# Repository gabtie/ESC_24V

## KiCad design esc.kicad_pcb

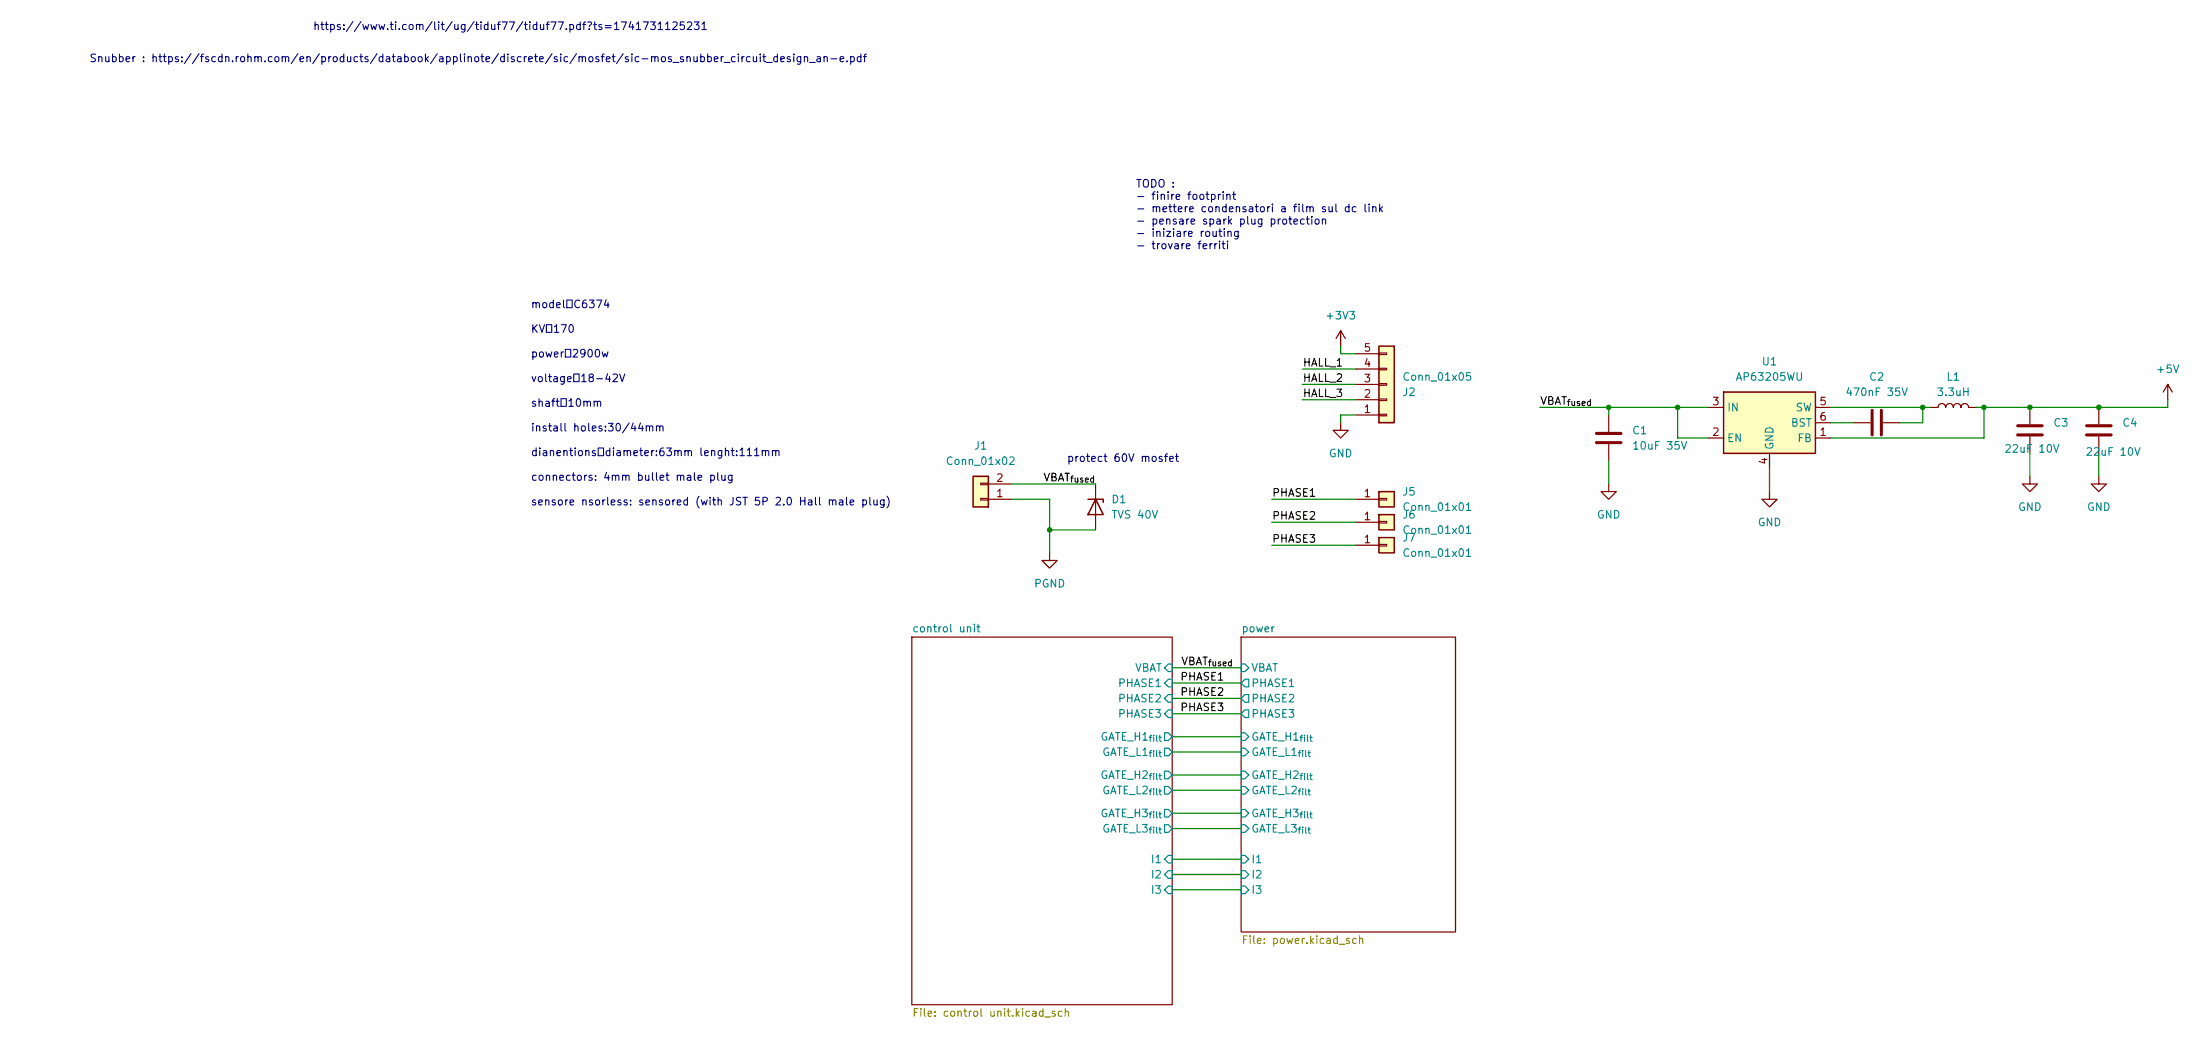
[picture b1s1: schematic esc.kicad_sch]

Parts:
C1: 10uF 35V; C_0603_1608Metric
C2: 470nF 35V; C_0603_1608Metric
C3, C4: 22uF 10V; C_0603_1608Metric
D1: TVS 40V; D_SMA
J1: Conn_01x02; AMASS_XT60-F_1x02_P7.20mm_Vertical
J2: Conn_01x05; JST_PH_B5B-PH-K_1x05_P2.00mm_Vertical
J5, J6, J7: Conn_01x01; MountingHole_3mm_Pad_Via
L1: 3.3uH; L_Wuerth_HCI-7040
U1: AP63205WU; TSOT-23-6

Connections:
+3V3: J2.5; also elsewhere on the board
+5V: C3.1, C4.1, L1.2, U1.1 (FB); also elsewhere on the board
/HALL_1: J2.4
/HALL_2: J2.3
/HALL_3: J2.2
/PHASE1: J5.1 (Pin_1_1); also elsewhere on the board
/PHASE2: J6.1 (Pin_1_1); also elsewhere on the board
/PHASE3: J7.1 (Pin_1_1); also elsewhere on the board
/VBAT_{fused}: C1.1, D1.1 (K), J1.2, U1.2 (EN), U1.3 (IN); also elsewhere on the board
GND: C1.2, C3.2, C4.2, J2.1, U1.4 (GND); also elsewhere on the board
unnamed: C2.1, U1.6 (BST)
unnamed: C2.2, L1.1, U1.5 (SW)
PGND: D1.2 (A), J1.1; also elsewhere on the board

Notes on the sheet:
https://www.ti.com/lit/ug/tiduf77/tiduf77.pdf?ts=1741731125231
model：C6374 KV：170 power：2900w voltage：18-42V shaft：10mm install holes:30/44mm dianentions：diameter:63mm lenght:111mm connectors: 4mm bullet male plug sensore nsorless: sensored (with JST 5P 2.0 Hall male plug)
protect 60V mosfet
Snubber : https://fscdn.rohm.com/en/products/databook/applinote/discrete/sic/mosfet/sic-mos_snubber_circuit_design_an-e.pdf
TODO : - finire footprint - mettere condensatori a film sul dc link - pensare spark plug protection - iniziare routing - trovare ferriti

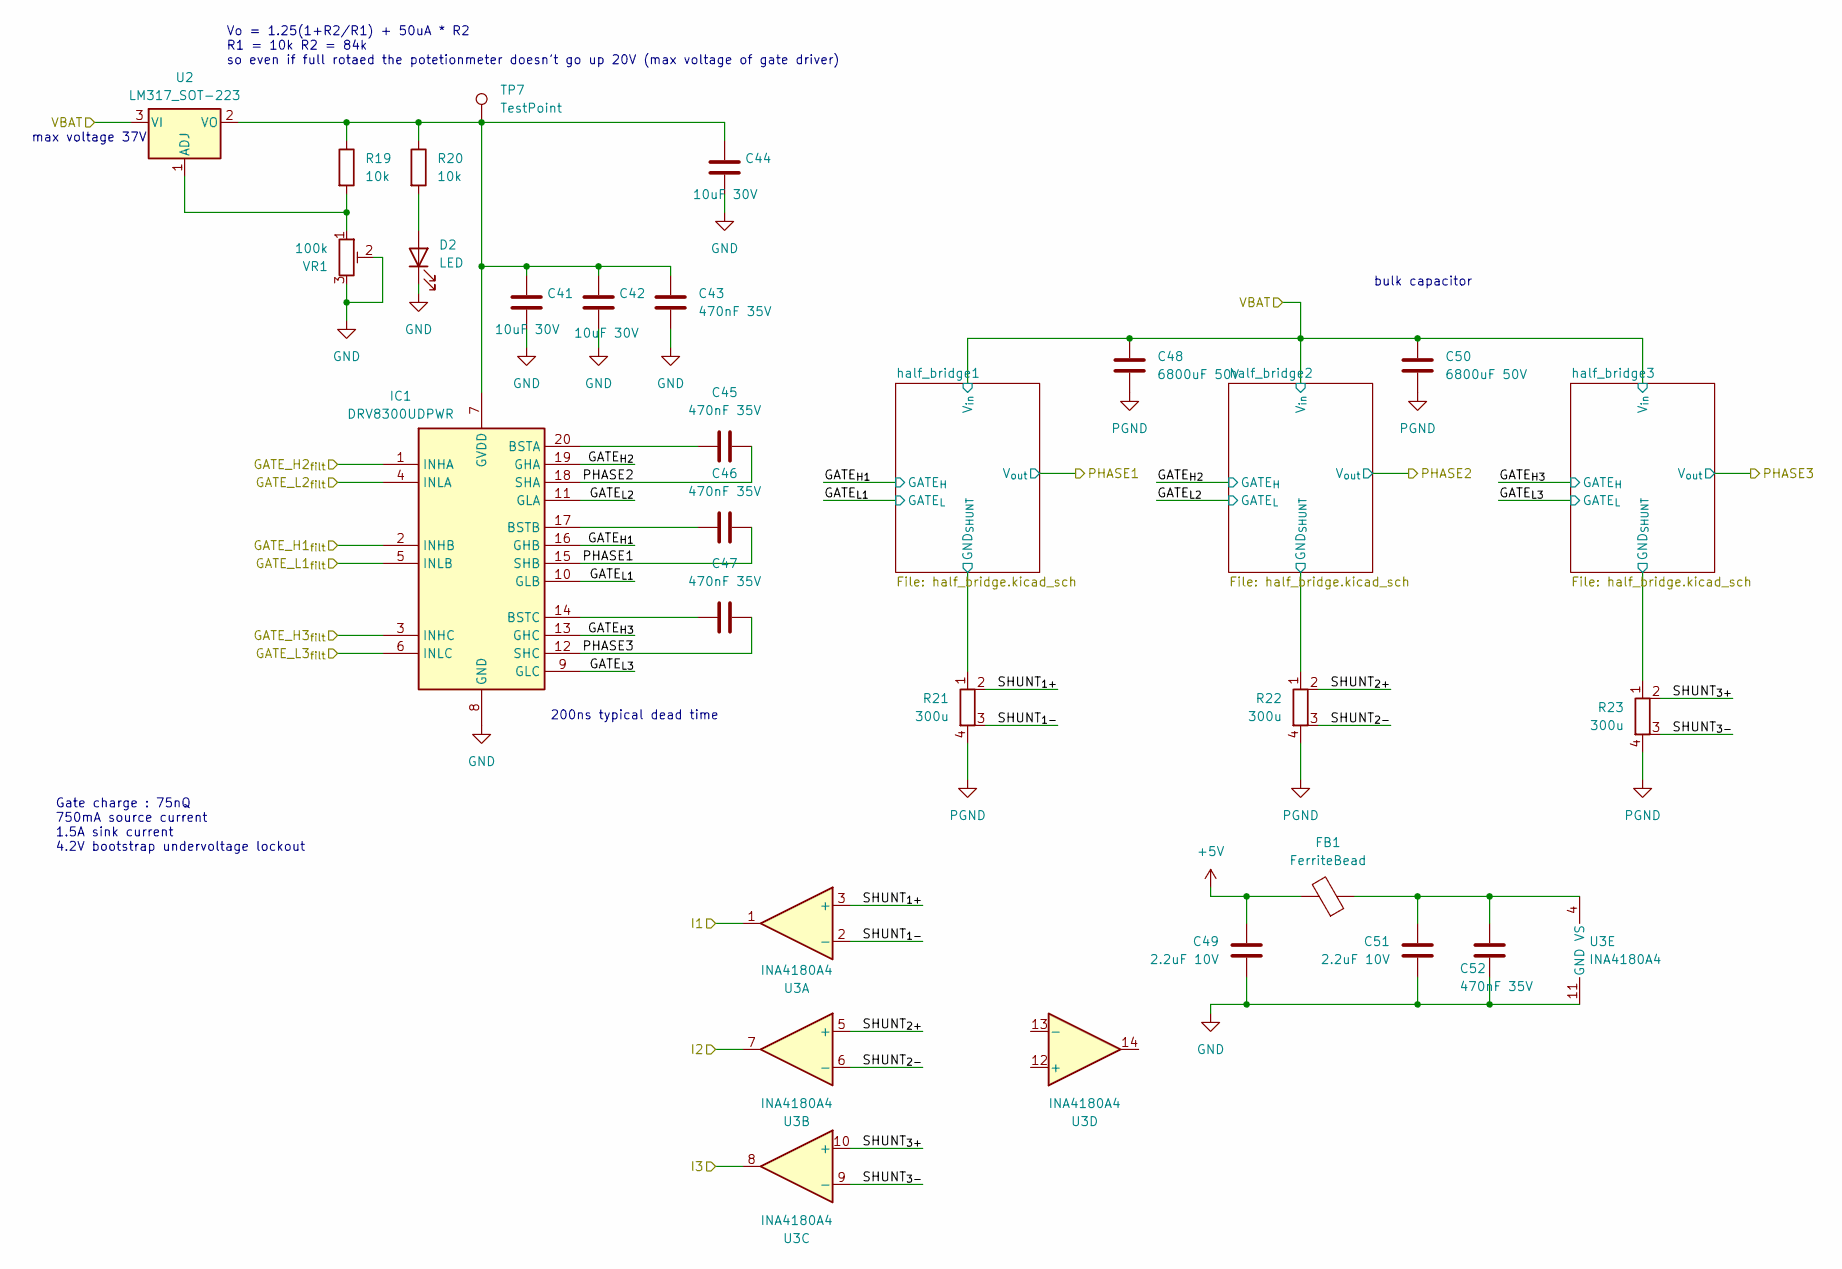
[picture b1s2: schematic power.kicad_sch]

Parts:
C41, C42: 10uF 30V; C_0603_1608Metric
C43, C45, C46, C47, C52: 470nF 35V; C_0603_1608Metric
C44: 10uF 30V; C_Radial_D5.0mm_H11.0mm_P2.00mm
C48, C50: 6800uF 50V; C_Radial_D18.0mm_H35.5mm_P7.50mm
C49, C51: 2.2uF 10V; C_0603_1608Metric
D2: LED; LED_0603_1608Metric
FB1: FerriteBead; L_0805_2012Metric
IC1: DRV8300UDPWR; gate_driver_SOP65P640X120-20N; Mouser Part Number 595-DRV8300UDPWR
R19, R20: 10k; R_0603_1608Metric
R21, R22, R23: 300u; HCSK1216FTL300
TP7: TestPoint; TestPoint_Pad_D1.0mm
U2: LM317_SOT-223; SOT-223-3_TabPin2
U3: INA4180A4; TSSOP-14_4.4x5mm_P0.65mm
VR1: 100k; Potentiometer_Bourns_3214W_Vertical

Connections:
+5V: C49.1, FB1.2; also elsewhere on the board
/PHASE1: C46.2, IC1.15 (SHB); also elsewhere on the board
/PHASE2: C45.2, IC1.18 (SHA); also elsewhere on the board
/PHASE3: C47.2, IC1.12 (SHC); also elsewhere on the board
/VBAT_{fused}: C48.1, C50.1, U2.3 (VI); also elsewhere on the board
/control unit/GATE_H1_{filt}: IC1.2 (INHB); also elsewhere on the board
/control unit/GATE_H2_{filt}: IC1.1 (INHA); also elsewhere on the board
/control unit/GATE_H3_{filt}: IC1.3 (INHC); also elsewhere on the board
/control unit/GATE_L1_{filt}: IC1.5 (INLB); also elsewhere on the board
/control unit/GATE_L2_{filt}: IC1.4 (INLA); also elsewhere on the board
/control unit/GATE_L3_{filt}: IC1.6 (INLC); also elsewhere on the board
/control unit/I1: U3.1; also elsewhere on the board
/control unit/I2: U3.7; also elsewhere on the board
/control unit/I3: U3.8; also elsewhere on the board
/power/GATE_{H1}: IC1.16 (GHB); also elsewhere on the board
/power/GATE_{H2}: IC1.19 (GHA); also elsewhere on the board
/power/GATE_{H3}: IC1.13 (GHC); also elsewhere on the board
/power/GATE_{L1}: IC1.10 (GLB); also elsewhere on the board
/power/GATE_{L2}: IC1.11 (GLA); also elsewhere on the board
/power/GATE_{L3}: IC1.9 (GLC); also elsewhere on the board
/power/SHUNT_{1+}: R21.2, U3.3 (+)
/power/SHUNT_{1-}: R21.3, U3.2 (-)
/power/SHUNT_{2+}: R22.2, U3.5 (+)
/power/SHUNT_{2-}: R22.3, U3.6 (-)
/power/SHUNT_{3+}: R23.2, U3.10 (+)
/power/SHUNT_{3-}: R23.3, U3.9 (-)
/power/half_bridge1/GND_{SHUNT}: R21.1; also elsewhere on the board
/power/half_bridge2/GND_{SHUNT}: R22.1; also elsewhere on the board
/power/half_bridge3/GND_{SHUNT}: R23.1; also elsewhere on the board
GND: C41.2, C42.2, C43.2, C44.2, C49.2, C51.2, C52.1, D2.1 (K), IC1.8 (GND), U3.11 (GND), VR1.2, VR1.3; also elsewhere on the board
unnamed: D2.2 (A), R20.2
unnamed: C45.1, IC1.20 (BSTA)
unnamed: C46.1, IC1.17 (BSTB)
unnamed: C47.1, IC1.14 (BSTC)
unnamed: C41.1, C42.1, C43.1, C44.1, IC1.7 (GVDD), R19.1, R20.1, TP7.1 (1_1), U2.2 (VO)
unnamed: R19.2, U2.1 (ADJ), VR1.1
unnamed: C51.1, C52.2, FB1.1, U3.4 (VS)
PGND: C48.2, C50.2, R21.4, R22.4, R23.4; also elsewhere on the board

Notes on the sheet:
max voltage 37V
bulk capacitor
Vo = 1.25(1+R2/R1) + 50uA * R2 R1 = 10k R2 = 84k so even if full rotaed the potetionmeter doesn't go up 20V (max voltage of gate driver)
200ns typical dead time
Gate charge : 75nQ 750mA source current 1.5A sink current 4.2V bootstrap undervoltage lockout

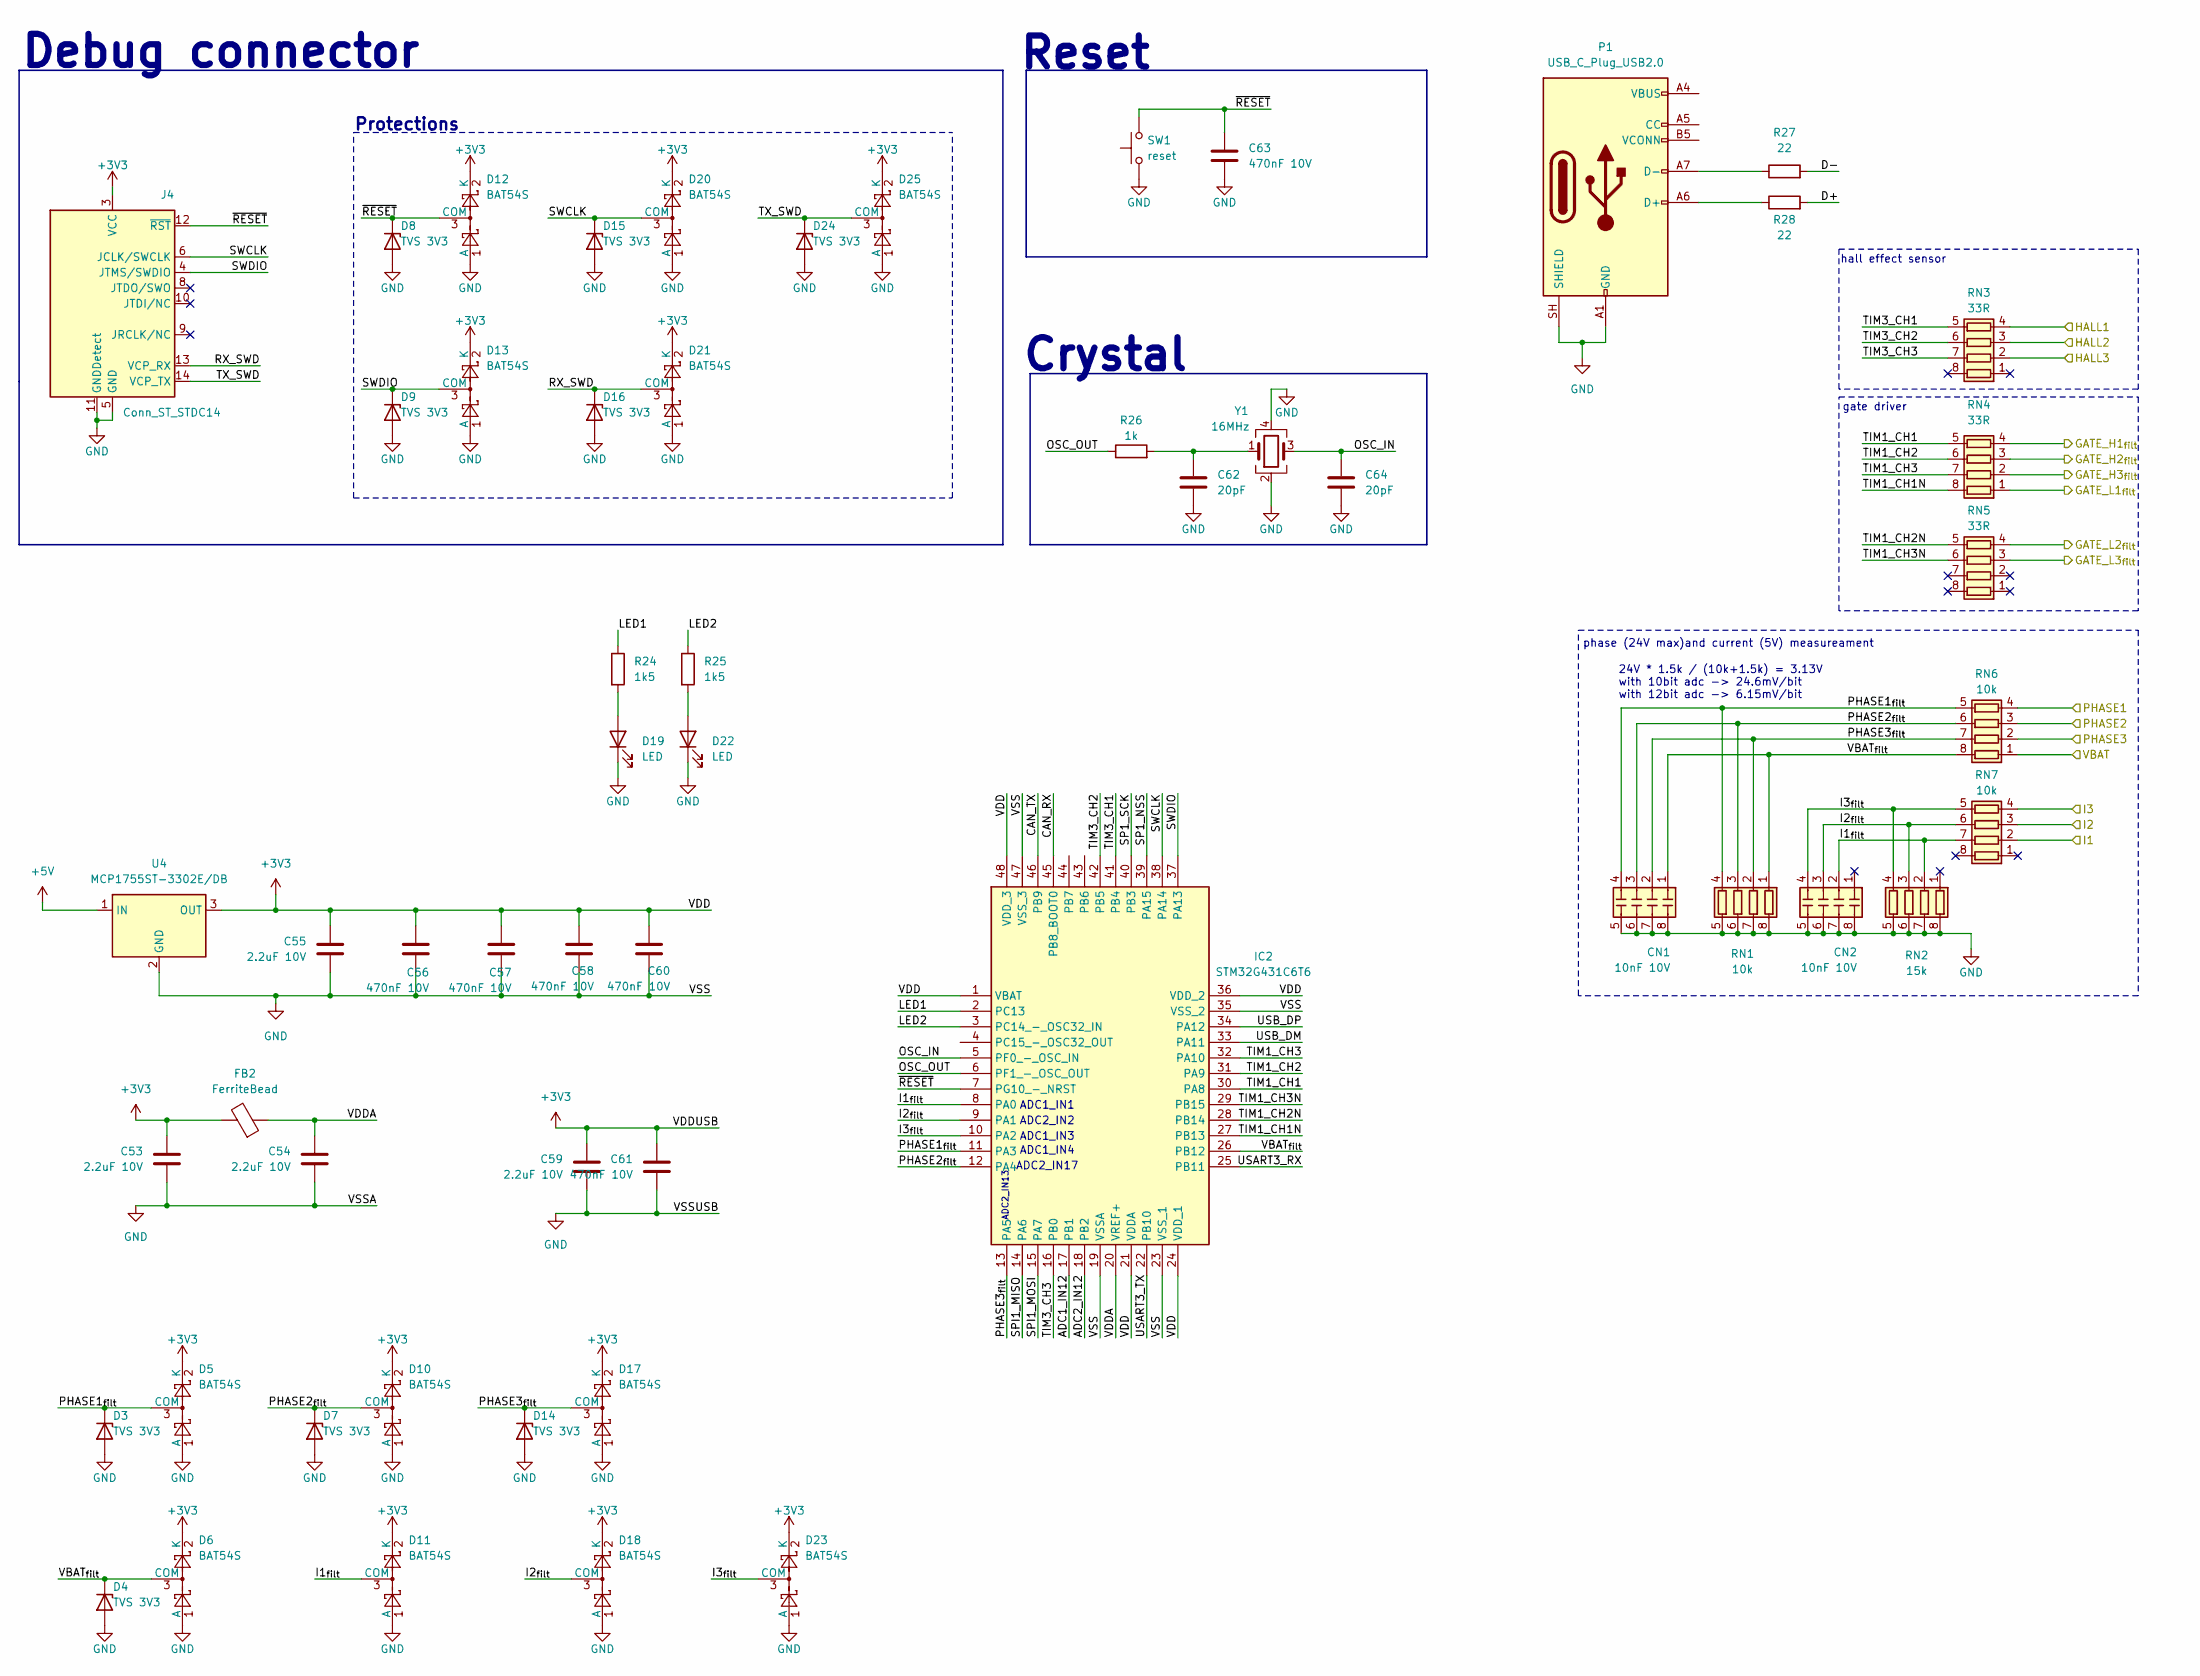
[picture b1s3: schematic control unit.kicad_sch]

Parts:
C53, C54, C55, C59: 2.2uF 10V; C_0603_1608Metric
C56, C57, C58, C60, C61, C63: 470nF 10V; C_0603_1608Metric
C62, C64: 20pF; C_0603_1608Metric
CN1, CN2: 10nF 10V; R_Array_Convex_4x0612
D3, D4, D7, D8, D9, D14, D15, D16, D24: TVS 3V3; D_SOD-523
D5, D6, D10, D11, D12, D13, D17, D18, D20, D21, D23, D25: BAT54S; SOT-23
D19, D22: LED; LED_0603_1608Metric
FB2: FerriteBead; L_0805_2012Metric
IC2: STM32G431C6T6; Mouser Part Number 511-STM32G431C6T6
J4: Conn_ST_STDC14; SAMTEC_FTSH-107-01-L-DV-K-TR
P1: USB_C_Plug_USB2.0
R24, R25: 1k5; R_0603_1608Metric
R26: 1k; R_0603_1608Metric
R27, R28: 22; R_0603_1608Metric
RN1, RN6, RN7: 10k; R_Array_Convex_4x0603
RN2: 15k; R_Array_Convex_4x0603
RN3, RN4, RN5: 33R; R_Array_Convex_4x0603
SW1: reset; SW_SPST_FSMSM
U4: MCP1755ST-3302E/DB; SOT-223-3_TabPin2
Y1: 16MHz; Crystal_SMD_EuroQuartz_MT-4Pin_3.2x2.5mm

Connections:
+3V3: C53.1, C55.1, C56.1, C57.1, C58.1, C59.1, C60.1, C61.1, D5.2 (K), D6.2 (K), D10.2 (K), D11.2 (K), D12.2 (K), D13.2 (K), D17.2 (K), D18.2 (K), D20.2 (K), D21.2 (K), D23.2 (K), D25.2 (K), FB2.2, IC2.1 (VBAT), IC2.21 (VDDA), IC2.24 (VDD_1), IC2.36 (VDD_2), IC2.48 (VDD_3), J4.3 (VCC), U4.3 (OUT); also elsewhere on the board
+5V: U4.1 (IN); also elsewhere on the board
/PHASE1: RN6.4 (R4.1); also elsewhere on the board
/PHASE2: RN6.3 (R3.1); also elsewhere on the board
/PHASE3: RN6.2 (R2.1); also elsewhere on the board
/VBAT_{fused}: RN6.1 (R1.1); also elsewhere on the board
/control unit/ADC1_IN12: IC2.17 (PB1)
/control unit/ADC2_IN12: IC2.18 (PB2)
/control unit/CAN_RX: IC2.45 (PB8_BOOT0)
/control unit/CAN_TX: IC2.46 (PB9)
/control unit/D+: R28.2
/control unit/D-: R27.2
/control unit/GATE_H1_{filt}: RN4.4 (R4.1); also elsewhere on the board
/control unit/GATE_H2_{filt}: RN4.3 (R3.1); also elsewhere on the board
/control unit/GATE_H3_{filt}: RN4.2 (R2.1); also elsewhere on the board
/control unit/GATE_L1_{filt}: RN4.1 (R1.1); also elsewhere on the board
/control unit/GATE_L2_{filt}: RN5.4 (R4.1); also elsewhere on the board
/control unit/GATE_L3_{filt}: RN5.3 (R3.1); also elsewhere on the board
/control unit/HALL1: RN3.4 (R4.1)
/control unit/HALL2: RN3.3 (R3.1)
/control unit/HALL3: RN3.2 (R2.1)
/control unit/I1: RN7.2 (R2.1); also elsewhere on the board
/control unit/I1_{filt}: CN2.2 (R2.1), D11.3 (COM), IC2.8 (PA0), RN2.2 (R2.1), RN7.7 (R2.2)
/control unit/I2: RN7.3 (R3.1); also elsewhere on the board
/control unit/I2_{filt}: CN2.3 (R3.1), D18.3 (COM), IC2.9 (PA1), RN2.3 (R3.1), RN7.6 (R3.2)
/control unit/I3: RN7.4 (R4.1); also elsewhere on the board
/control unit/I3_{filt}: CN2.4 (R4.1), D23.3 (COM), IC2.10 (PA2), RN2.4 (R4.1), RN7.5 (R4.2)
/control unit/LED1: IC2.2 (PC13), R24.1
/control unit/LED2: IC2.3 (PC14_-_OSC32_IN), R25.1
/control unit/OSC_IN: C64.1, IC2.5 (PF0_-_OSC_IN), Y1.3
/control unit/OSC_OUT: IC2.6 (PF1_-_OSC_OUT), R26.1
/control unit/PHASE1_{filt}: CN1.4 (R4.1), D3.1 (K), D5.3 (COM), IC2.11 (PA3), RN1.4 (R4.1), RN6.5 (R4.2)
/control unit/PHASE2_{filt}: CN1.3 (R3.1), D7.1 (K), D10.3 (COM), IC2.12 (PA4), RN1.3 (R3.1), RN6.6 (R3.2)
/control unit/PHASE3_{filt}: CN1.2 (R2.1), D14.1 (K), D17.3 (COM), IC2.13 (PA5), RN1.2 (R2.1), RN6.7 (R2.2)
/control unit/RX_SWD: D16.1 (K), D21.3 (COM), J4.13 (VCP_RX)
/control unit/SP1_NSS: IC2.39 (PA15)
/control unit/SP1_SCK: IC2.40 (PB3)
/control unit/SPI1_MISO: IC2.14 (PA6)
/control unit/SPI1_MOSI: IC2.15 (PA7)
/control unit/SWCLK: D15.1 (K), D20.3 (COM), IC2.38 (PA14), J4.6 (JCLK/SWCLK)
/control unit/SWDIO: D9.1 (K), D13.3 (COM), IC2.37 (PA13), J4.4 (JTMS/SWDIO)
/control unit/TIM1_CH1: IC2.30 (PA8), RN4.5 (R4.2)
/control unit/TIM1_CH1N: IC2.27 (PB13), RN4.8 (R1.2)
/control unit/TIM1_CH2: IC2.31 (PA9), RN4.6 (R3.2)
/control unit/TIM1_CH2N: IC2.28 (PB14), RN5.5 (R4.2)
/control unit/TIM1_CH3: IC2.32 (PA10), RN4.7 (R2.2)
/control unit/TIM1_CH3N: IC2.29 (PB15), RN5.6 (R3.2)
/control unit/TIM3_CH1: IC2.41 (PB4), RN3.5 (R4.2)
/control unit/TIM3_CH2: IC2.42 (PB5), RN3.6 (R3.2)
/control unit/TIM3_CH3: IC2.16 (PB0), RN3.7 (R2.2)
/control unit/TX_SWD: D24.1 (K), D25.3 (COM), J4.14 (VCP_TX)
/control unit/USART3_RX: IC2.25 (PB11)
/control unit/USART3_TX: IC2.22 (PB10)
/control unit/USB_DM: IC2.33 (PA11)
/control unit/USB_DP: IC2.34 (PA12)
/control unit/VBAT_{filt}: CN1.1 (R1.1), D4.1 (K), D6.3 (COM), IC2.26 (PB12), RN1.1 (R1.1), RN6.8 (R1.2)
/control unit/VDDA: C54.1, FB2.1, IC2.20 (VREF+)
/control unit/~RESET: C63.1, D8.1 (K), D12.3 (COM), IC2.7 (PG10_-_NRST), J4.12 (~RST), SW1.2
GND: C53.2, C54.2, C55.2, C56.2, C57.2, C58.2, C59.2, C60.2, C61.2, C62.2, C63.2, C64.2, CN1.5 (R4.2), CN1.6 (R3.2), CN1.7 (R2.2), CN1.8 (R1.2), CN2.5 (R4.2), CN2.6 (R3.2), CN2.7 (R2.2), CN2.8 (R1.2), D3.2 (A), D4.2 (A), D5.1 (A), D6.1 (A), D7.2 (A), D8.2 (A), D9.2 (A), D10.1 (A), D11.1 (A), D12.1 (A), D13.1 (A), D14.2 (A), D15.2 (A), D16.2 (A), D17.1 (A), D18.1 (A), D19.1 (K), D20.1 (A), D21.1 (A), D22.1 (K), D23.1 (A), D24.2 (A), D25.1 (A), IC2.19 (VSSA), IC2.23 (VSS_1), IC2.35 (VSS_2), IC2.47 (VSS_3), J4.5 (GND), J4.7 (GND), J4.11 (GNDDetect), P1.A1 (GND), P1.A12 (GND), P1.B1 (GND), P1.B12 (GND), P1.SH (SHIELD), RN1.5 (R4.2), RN1.6 (R3.2), RN1.7 (R2.2), RN1.8 (R1.2), RN2.5 (R4.2), RN2.6 (R3.2), RN2.7 (R2.2), RN2.8 (R1.2), SW1.1, U4.2 (GND), Y1.2, Y1.4; also elsewhere on the board
unnamed: C62.1, R26.2, Y1.1
unnamed: D19.2 (A), R24.2
unnamed: D22.2 (A), R25.2
unnamed: P1.A6 (D+), R28.1
unnamed: P1.A7 (D-), R27.1
unnamed: P1.A4 (VBUS), P1.A9 (VBUS), P1.B4 (VBUS), P1.B9 (VBUS)

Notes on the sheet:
ADC2_IN2
Reset
hall effect sensor
phase (24V max)and current (5V) measureament
gate driver
ADC1_IN3
24V * 1.5k / (10k+1.5k) = 3.13V with 10bit adc -> 24.6mV/bit with 12bit adc -> 6.15mV/bit
Crystal
Protections
ADC2_IN17
ADC1_IN1
ADC1_IN4
ADC2_IN13
Debug connector

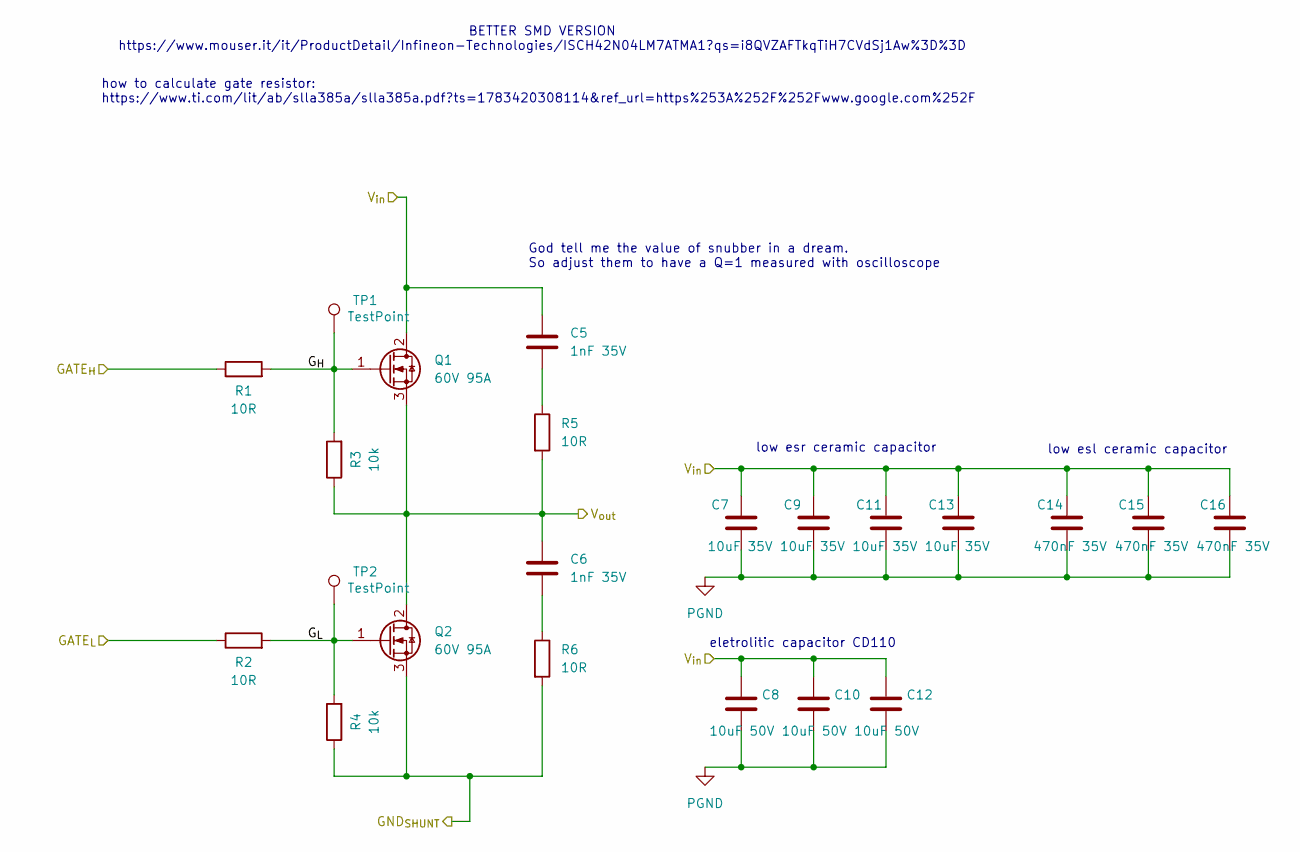
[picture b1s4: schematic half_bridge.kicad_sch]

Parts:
C5, C6: 1nF 35V; C_0603_1608Metric
C7, C9, C11, C13: 10uF 35V; C_1206_3216Metric
C8, C10, C12: 10uF 50V; C_Radial_D5.0mm_H11.0mm_P2.00mm
C14, C15, C16: 470nF 35V; C_0603_1608Metric
Q1, Q2: 60V 95A; TO-220-3_Vertical
R1, R2, R5, R6: 10R; R_0603_1608Metric
R3, R4: 10k; R_0603_1608Metric
TP1, TP2: TestPoint; TestPoint_Pad_D1.0mm

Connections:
/PHASE1: C6.1, Q1.3 (S), Q2.2 (D), R3.1, R5.2; also elsewhere on the board
/VBAT_{fused}: C5.1, C7.1, C8.1, C9.1, C10.1, C11.1, C12.1, C13.1, C14.1, C15.1, C16.1, Q1.2 (D); also elsewhere on the board
/power/GATE_{H1}: R1.1; also elsewhere on the board
/power/GATE_{L1}: R2.1; also elsewhere on the board
/power/half_bridge1/GND_{SHUNT}: Q2.3 (S), R4.1, R6.2; also elsewhere on the board
/power/half_bridge1/G_{H}: Q1.1 (G), R1.2, R3.2, TP1.1 (1_1)
/power/half_bridge1/G_{L}: Q2.1 (G), R2.2, R4.2, TP2.1 (1_1)
unnamed: C5.2, R5.1
unnamed: C6.2, R6.1
PGND: C7.2, C8.2, C9.2, C10.2, C11.2, C12.2, C13.2, C14.2, C15.2, C16.2; also elsewhere on the board

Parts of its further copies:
C17, C18, C29, C30: 1nF 35V; C_0603_1608Metric
C19, C21, C23, C25, C31, C33, C35, C37: 10uF 35V; C_1206_3216Metric
C20, C22, C24, C32, C34, C36: 10uF 50V; C_Radial_D5.0mm_H11.0mm_P2.00mm
C26, C27, C28, C38, C39, C40: 470nF 35V; C_0603_1608Metric
Q3, Q4, Q5, Q6: 60V 95A; TO-220-3_Vertical
R7, R8, R11, R12, R13, R14, R17, R18: 10R; R_0603_1608Metric
R9, R10, R15, R16: 10k; R_0603_1608Metric
TP3, TP4, TP5, TP6: TestPoint; TestPoint_Pad_D1.0mm

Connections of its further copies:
/PHASE2: C18.1, Q3.3 (S), Q4.2 (D), R9.1, R11.2; also elsewhere on the board
/PHASE3: C30.1, Q5.3 (S), Q6.2 (D), R15.1, R17.2; also elsewhere on the board
/VBAT_{fused}: C17.1, C19.1, C20.1, C21.1, C22.1, C23.1, C24.1, C25.1, C26.1, C27.1, C28.1, C29.1, C31.1, C32.1, C33.1, C34.1, C35.1, C36.1, C37.1, C38.1, C39.1, C40.1, Q3.2 (D), Q5.2 (D); also elsewhere on the board
/power/GATE_{H2}: R7.1; also elsewhere on the board
/power/GATE_{H3}: R13.1; also elsewhere on the board
/power/GATE_{L2}: R8.1; also elsewhere on the board
/power/GATE_{L3}: R14.1; also elsewhere on the board
/power/half_bridge2/GND_{SHUNT}: Q4.3 (S), R10.1, R12.2; also elsewhere on the board
/power/half_bridge2/G_{H}: Q3.1 (G), R7.2, R9.2, TP3.1 (1_1)
/power/half_bridge2/G_{L}: Q4.1 (G), R8.2, R10.2, TP4.1 (1_1)
/power/half_bridge3/GND_{SHUNT}: Q6.3 (S), R16.1, R18.2; also elsewhere on the board
/power/half_bridge3/G_{H}: Q5.1 (G), R13.2, R15.2, TP5.1 (1_1)
/power/half_bridge3/G_{L}: Q6.1 (G), R14.2, R16.2, TP6.1 (1_1)
unnamed: C17.2, R11.1
unnamed: C18.2, R12.1
unnamed: C29.2, R17.1
unnamed: C30.2, R18.1
PGND: C19.2, C20.2, C21.2, C22.2, C23.2, C24.2, C25.2, C26.2, C27.2, C28.2, C31.2, C32.2, C33.2, C34.2, C35.2, C36.2, C37.2, C38.2, C39.2, C40.2; also elsewhere on the board

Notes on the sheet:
eletrolitic capacitor CD110
low esr ceramic capacitor
low esl ceramic capacitor
God tell me the value of snubber in a dream. So adjust them to have a Q=1 measured with oscilloscope
BETTER SMD VERSION https://www.mouser.it/it/ProductDetail/Infineon-Technologies/ISCH42N04LM7ATMA1?qs=i8QVZAFTkqTiH7CVdSj1Aw%3D%3D
how to calculate gate resistor: https://www.ti.com/lit/ab/slla385a/slla385a.pdf?ts=1783420308114&ref_url=https%253A%252F%252Fwww.google.com%252F

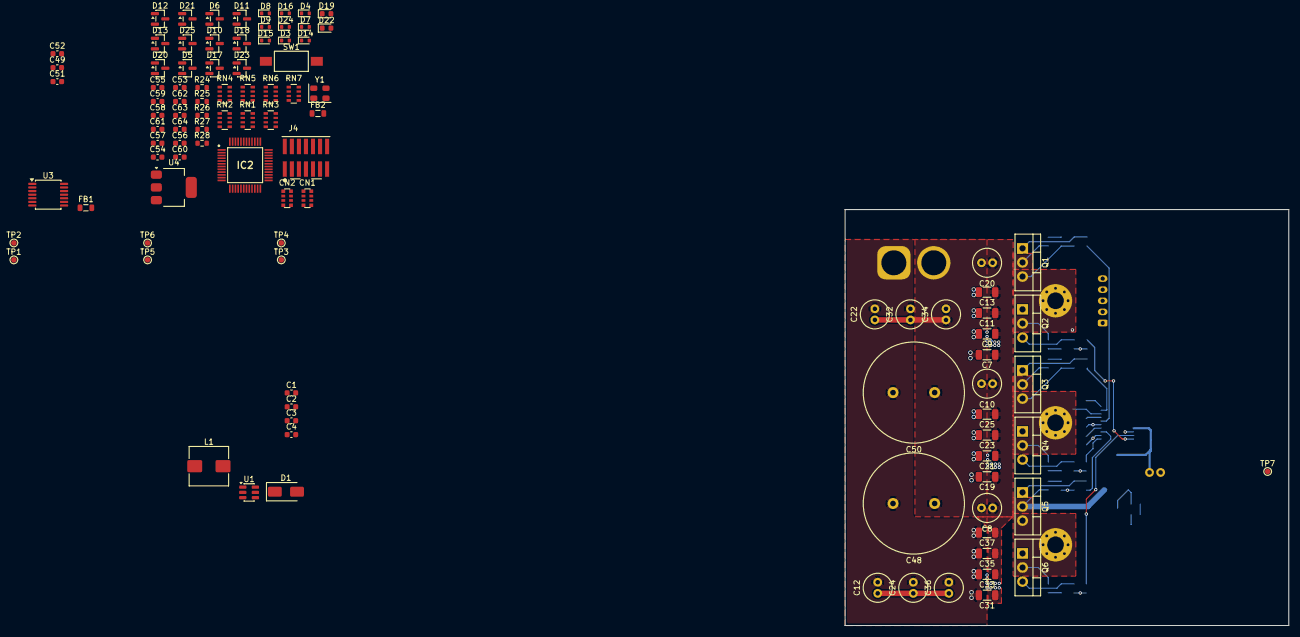
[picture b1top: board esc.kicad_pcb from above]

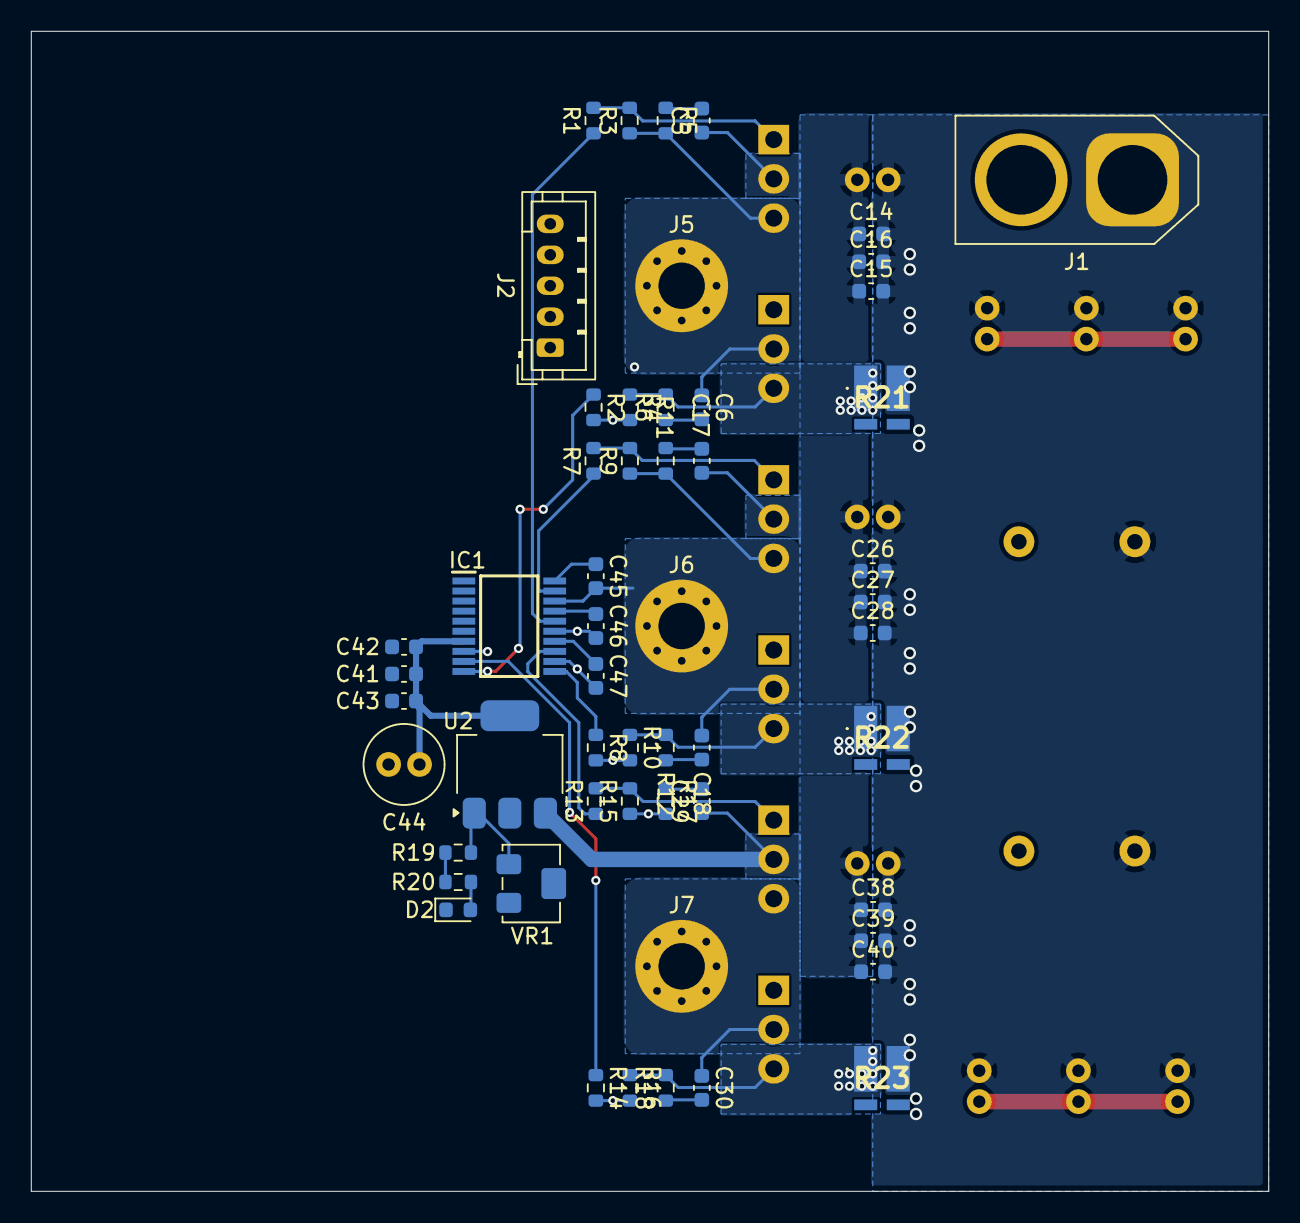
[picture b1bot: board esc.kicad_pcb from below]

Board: 4 copper layers, 80.0 x 75.0 mm, 157 parts (54 on the bottom side), 82 nets.

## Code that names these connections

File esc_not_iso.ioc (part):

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Mcu.Name=STM32G431C(6-8-B)Tx
Mcu.Package=LQFP48
Mcu.UserName=STM32G431C6Tx
PA0.GPIOParameters=GPIO_Label
PA0.GPIO_Label=I1
PA0.Signal=SharedAnalog_PA0
PA1.GPIOParameters=GPIO_Label
PA1.GPIO_Label=I2
PA1.Signal=SharedAnalog_PA1
PA10.Signal=S_TIM1_CH3
PA11.Mode=Device
PA11.Signal=USB_DM
PA12.Mode=Device
PA12.Signal=USB_DP
PA13.Mode=Serial_Wire
PA13.Signal=SYS_JTMS-SWDIO
PA14.Mode=Serial_Wire
PA14.Signal=SYS_JTCK-SWCLK
PA15.Mode=NSS_Signal_Hard_Output
PA15.Signal=SPI1_NSS
PA2.GPIOParameters=GPIO_Label
PA2.GPIO_Label=PHASE1
PA2.Mode=IN3-Single-Ended
PA2.Signal=ADC1_IN3
PA3.GPIOParameters=GPIO_Label
PA3.GPIO_Label=I3
PA3.Signal=SharedAnalog_PA3
PA4.GPIOParameters=GPIO_Label
PA4.GPIO_Label=PHASE2
PA4.Mode=IN17-Single-Ended
PA4.Signal=ADC2_IN17
PA5.GPIOParameters=GPIO_Label
PA5.GPIO_Label=PHASE3
PA5.Mode=IN13-Single-Ended
PA5.Signal=ADC2_IN13
PA6.Mode=Full_Duplex_Master
PA6.Signal=SPI1_MISO
PA7.Mode=Full_Duplex_Master
PA7.Signal=SPI1_MOSI
PA8.Signal=S_TIM1_CH1
PA9.Signal=S_TIM1_CH2
PB0.Signal=S_TIM3_CH3
PB1.Mode=IN12-Single-Ended
PB1.Signal=ADC1_IN12
PB10.Mode=Asynchronous
PB10.Signal=USART3_TX
PB11.Mode=Asynchronous
PB11.Signal=USART3_RX
PB12.GPIOParameters=GPIO_Label
PB12.GPIO_Label=VBAT
PB12.Mode=IN11-Single-Ended
PB12.Signal=ADC1_IN11
PB13.Mode=PWM Generation1 CH1 CH1N
PB13.Signal=TIM1_CH1N
PB14.Mode=PWM Generation2 CH2 CH2N
PB14.Signal=TIM1_CH2N
PB15.Mode=PWM Generation3 CH3 CH3N
PB15.Signal=TIM1_CH3N
PB2.Mode=IN12-Single-Ended
PB2.Signal=ADC2_IN12
PB3.Mode=Full_Duplex_Master
PB3.Signal=SPI1_SCK
PB4.Signal=S_TIM3_CH1
PB5.Signal=S_TIM3_CH2
PB8-BOOT0.Mode=FDCAN_Activate
PB8-BOOT0.Signal=FDCAN1_RX
PB9.Mode=FDCAN_Activate
PB9.Signal=FDCAN1_TX
PC13.Mode=Activate-Break-Input
PC13.Signal=TIM1_BKIN
PC14-OSC32_IN.GPIOParameters=GPIO_Label
PC14-OSC32_IN.GPIO_Label=LED1
PC14-OSC32_IN.Signal=GPIO_Output
PC15-OSC32_OUT.GPIOParameters=GPIO_Label
PC15-OSC32_OUT.GPIO_Label=LED2
PC15-OSC32_OUT.Signal=GPIO_Output
PF0-OSC_IN.Mode=HSE-External-Oscillator
PF0-OSC_IN.Signal=RCC_OSC_IN
PF1-OSC_OUT.Mode=HSE-External-Oscillator
PF1-OSC_OUT.Signal=RCC_OSC_OUT
RCC.HSE_VALUE=16000000
RCC.SYSCLKFreq_VALUE=168000000
RCC.SYSCLKSource=RCC_SYSCLKSOURCE_PLLCLK
board=custom
